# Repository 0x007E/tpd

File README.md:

# `TPD` - Touchpad

The `TPD` is a board with six single pads that are connected to a [AT42QT1070](#additional-information) touch sensor. The touch sensor can be connected to any microntroller over `TWI`. The board itself can be driven with a voltage from `1V8-5V` and controlled over the [AT42QTXXXX driver library](https://github.com/0x007E/drivers-touch-at42qtxxxx).

| Experience  | Level                                                                               |
|:------------|:-----------------------------------------------------------------------------------:|
| Soldering   |  |
| Mechanical  |  |

# Downloads

| Type      | File                                                                                                                                                 | Description     |
|:---------:|:----------------------------------------------------------------------------------------------------------------------------------------------------:|:----------------|
| Schematic | [pdf](https://github.com/0x007E/tpd/releases/latest/download/schematic.pdf) / [cadlab](https://cadlab.io/project/30134/main/files)                   | Schematic files |
| Board     | [pdf](https://github.com/0x007E/tpd/releases/latest/download/pcb.pdf) / [cadlab](https://cadlab.io/project/30134/main/files)                         | Board file      |
| Drill     | [pdf](https://github.com/0x007E/tpd/releases/latest/download/drill.pdf)                                                                              | Drill file      |
| BoM | [xlsx](https://github.com/0x007E/tpd/releases/latest/download/bom.xlsx) / [html](https://github.com/0x007E/tpd/releases/latest/download/ibom.html)          | Bill of Material as Excel/interactive HTML |
| PCB    | [zip](https://github.com/0x007E/tpd/releases/latest/download/kicad.zip) / [tar](https://github.com/0x007E/tpd/releases/latest/download/kicad.tar.gz)    | KiCAD/Gerber/BoM/Drill files       |
| Mechanical | [zip](https://github.com/0x007E/tpd/releases/latest/download/freecad.zip) / [tar](https://github.com/0x007E/tpd/releases/latest/download/freecad.tar.gz) | FreeCAD/Housing and PCB (STEP/STL) files     |

# Hardware

The pcb is created with `KiCAD`. All files are built with `github actions` so that they are ready for a production environment.

## PCB

The circuit board is populated on one side (Bottom). The best way for soldering the `SMD` components is within a vapor phase soldering system.

### Top Layer

### Bottom Layer

## Mechanical

The housing has a tolerance of `0.2mm` on each side of the case. So the pcb should fit perfectly in the housing. The tolerance can be modified with `FreeCAD` in the `Parameter` Spreadsheet.

### Assembled

### Exploded

# Additional Information

| Type       | Link                                                                                                      | Description                                        |
|:----------:|:---------------------------------------------------------------------------------------------------------:|:---------------------------------------------------|
| AT42QT1070   | [pdf](https://ww1.microchip.com/downloads/en/DeviceDoc/Atmel-9596-AT42-QTouch-BSW-AT42QT1070_Datasheet.pdf) | Seven-channel QTouch® Touch Sensor IC |

---

R. GAECHTER

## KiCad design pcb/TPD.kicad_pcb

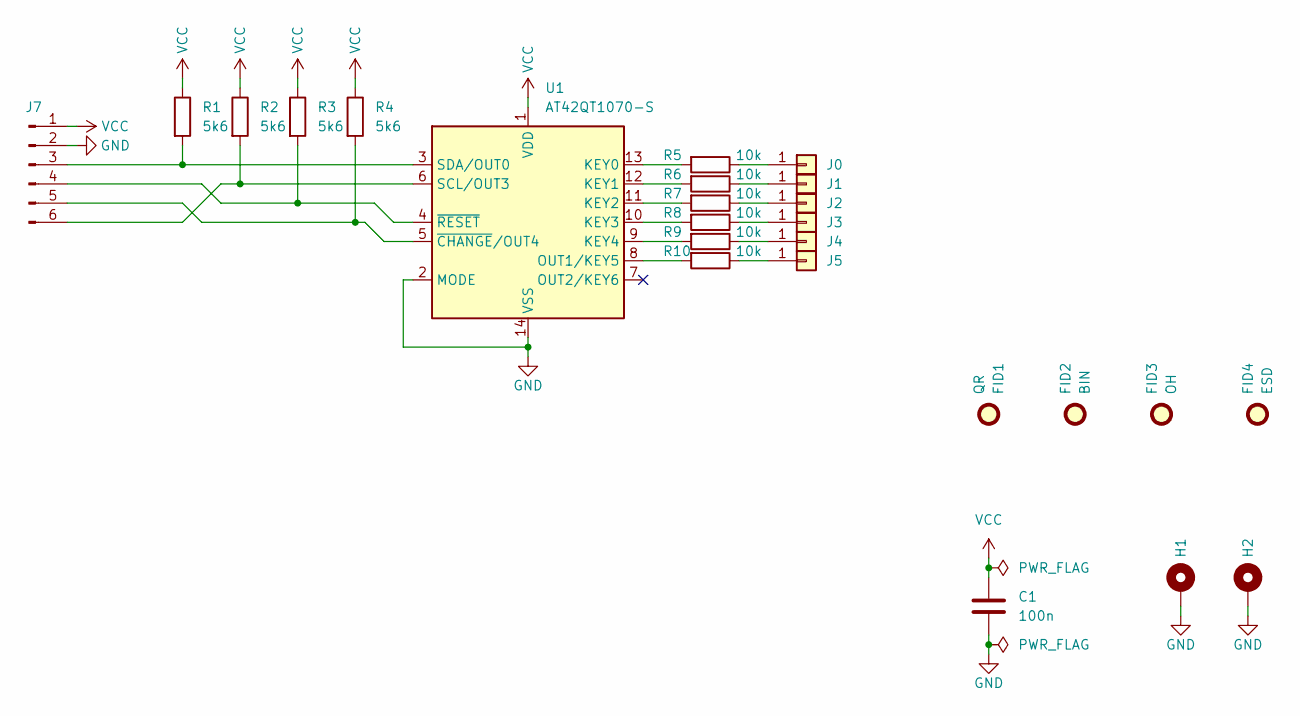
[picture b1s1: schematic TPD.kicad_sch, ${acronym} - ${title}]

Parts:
C1: 100n; C_1206_3216Metric
FID1: QR; QR_0x007e_very_small
FID2: BIN; WEEE-Logo_4.2x6mm_SilkScreen
FID3: OH; OSHW-Logo2_7.3x6mm_SilkScreen
FID4: ESD; ESD-Logo_6.6x6mm_SilkScreen
H1, H2: MountingHole_Pad; MountingHole_2.2mm_M2_Pad
J0, J1, J2, J3, J4, J5: Conn_01x01; Button_Round_Small
J7: Conn_01x06_Pin; PinHeader_1x06_P2.54mm_Vertical_SMD_Pin1Left
R1, R2, R3, R4: 5k6; R_1206_3216Metric
R5, R6, R7, R8, R9, R10: 10k; R_1206_3216Metric
U1: AT42QT1070-S; SOIC-14_3.9x8.7mm_P1.27mm

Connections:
GND: C1.2, H1.1, H2.1, J7.2, U1.2 (MODE), U1.14 (VSS)
unnamed: J0.1, R5.1
unnamed: J1.1, R6.1
unnamed: J2.1, R7.1
unnamed: J3.1, R8.1
unnamed: J4.1, R9.1
unnamed: J5.1, R10.1
unnamed: J7.3, R1.2, U1.3 (SDA/OUT0)
unnamed: J7.4, R3.2, U1.4 (~RESET)
unnamed: J7.5, R4.2, U1.5 (~CHANGE/OUT4)
unnamed: J7.6, R2.2, U1.6 (SCL/OUT3)
unnamed: R5.2, U1.13 (KEY0)
unnamed: R6.2, U1.12 (KEY1)
unnamed: R7.2, U1.11 (KEY2)
unnamed: R8.2, U1.10 (KEY3)
unnamed: R9.2, U1.9 (KEY4)
unnamed: R10.2, U1.8 (OUT1/KEY5)
VCC: C1.1, J7.1, R1.1, R2.1, R3.1, R4.1, U1.1 (VDD)

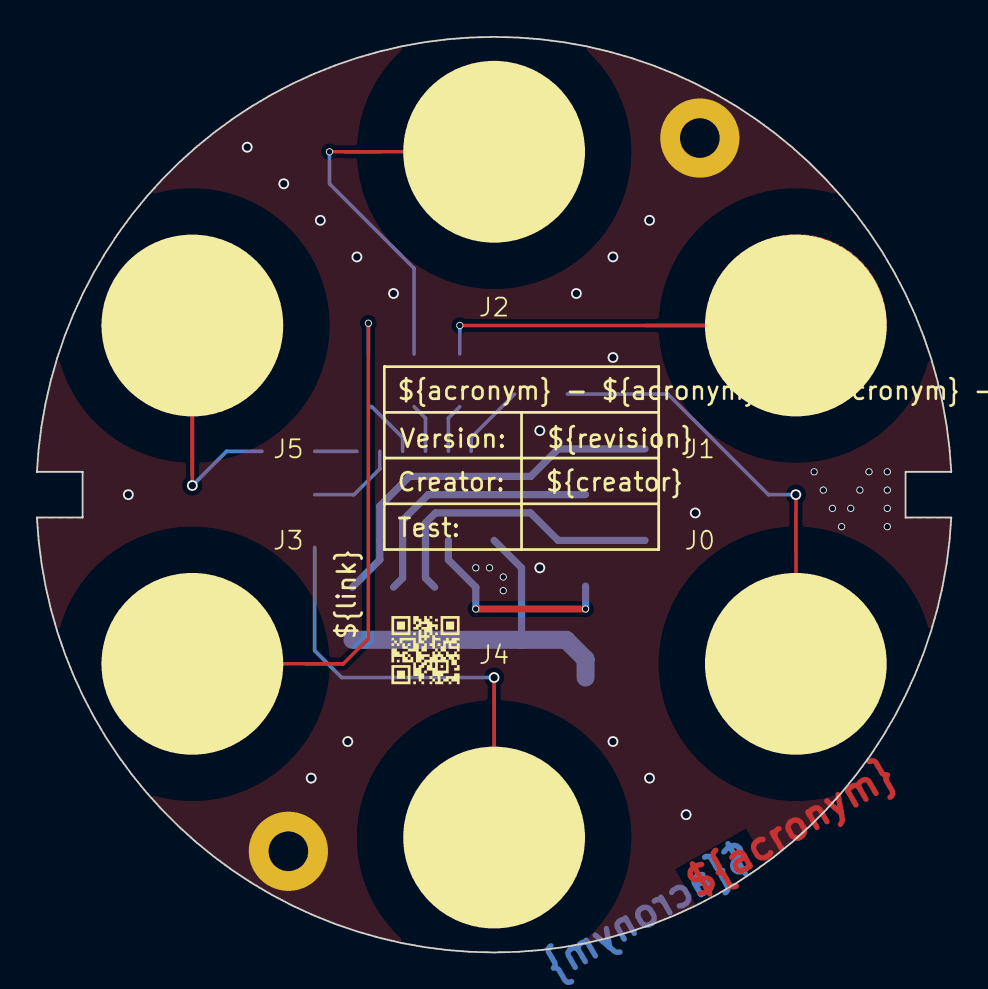
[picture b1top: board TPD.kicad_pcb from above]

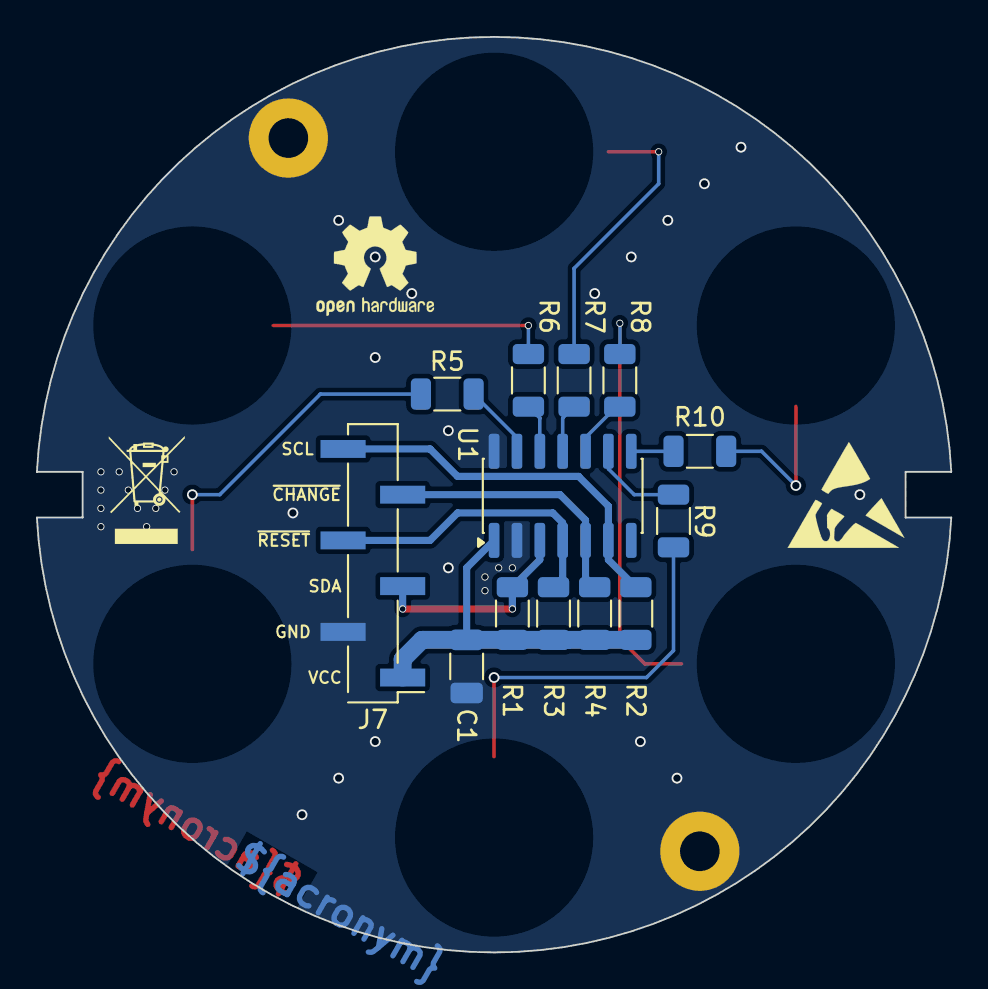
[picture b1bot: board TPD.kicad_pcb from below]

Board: 2 copper layers, 50.8 x 50.9 mm, 25 parts (16 on the bottom side), 18 nets.

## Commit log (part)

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2026-03-05 Add pcb layout
2026-03-05 Add README.md
2026-03-05 Add build pipeline
2026-03-05 Add release pipeline
2026-03-05 Add missing vendors
2026-03-26 Add pin names to silkscreen
2026-04-01 Add dimensioning
2026-04-22 Adapt vendor(id)

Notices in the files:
README.md:
License CC By-NC-SA
parts and their libraries:
license: CC BY-NC-SA 4.0
